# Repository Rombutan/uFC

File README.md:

# uFC

A baby flight controller main board optimized for small unpowered creations, powered by the esp32 and mpu6050.
Will soon have a camera connector.

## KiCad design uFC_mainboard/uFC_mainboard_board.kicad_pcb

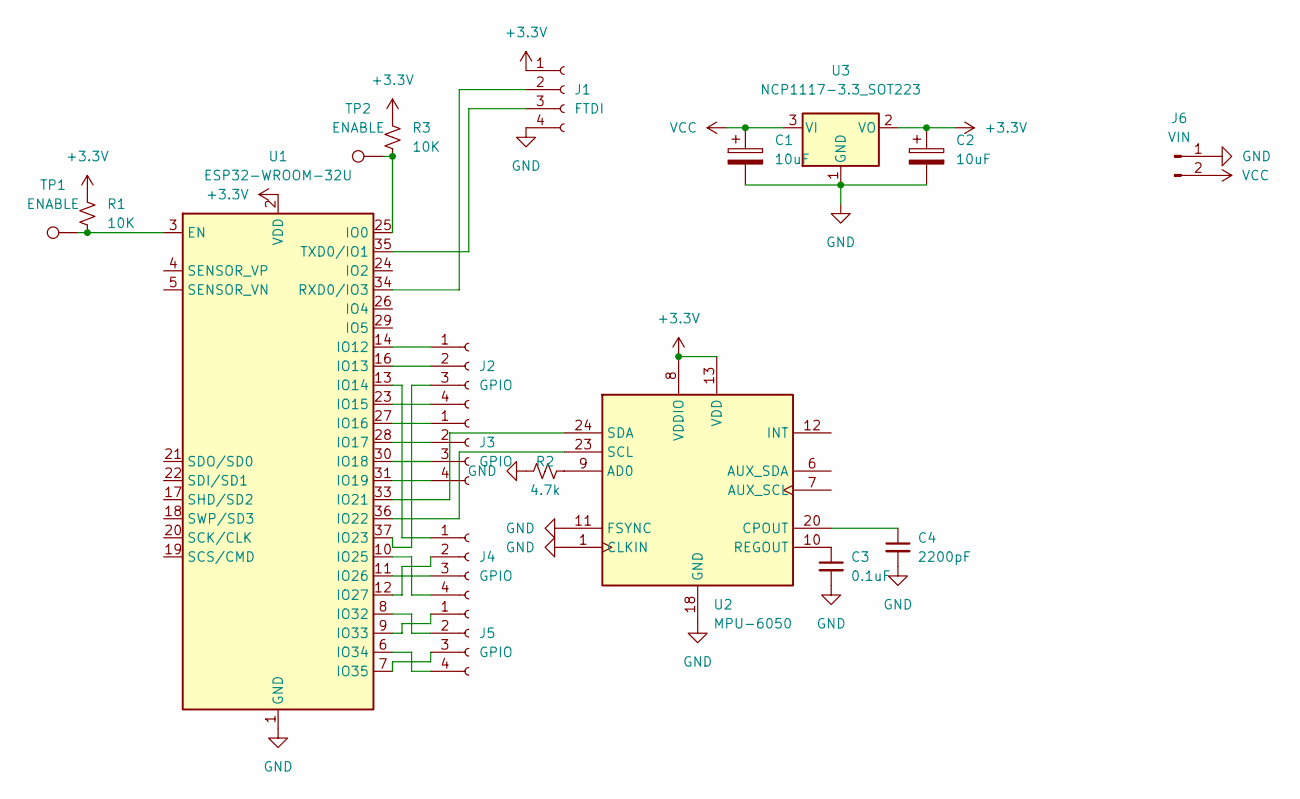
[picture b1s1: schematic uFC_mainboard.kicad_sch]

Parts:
C1, C2: 10uF; CP_Elec_4x5.3
C3: 0.1uF; C_0402_1005Metric
C4: 2200pF; C_0402_1005Metric
J1: FTDI; PinHeader_1x04_P2.54mm_Vertical
J2, J3, J4, J5: GPIO; PinHeader_1x04_P2.54mm_Vertical
J6: VIN; PinHeader_1x02_P2.54mm_Vertical
R1, R3: 10K; R_0402_1005Metric
R2: 4.7k; R_0402_1005Metric
TP1, TP2: ENABLE; PinHeader_1x01_P2.54mm_Vertical
U1: ESP32-WROOM-32U
U2: MPU-6050; InvenSense_QFN-24_4x4mm_P0.5mm
U3: NCP1117-3.3_SOT223; SOT-223-3_TabPin2

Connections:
+3V3: C2.1, J1.1, R1.1, R3.1, U1.2 (VDD), U2.8 (VDDIO), U2.13 (VDD), U3.2 (VO)
GND: C1.2, C2.2, C3.2, C4.2, J1.4, J6.1, R2.1, U1.1 (GND), U1.15 (GND), U1.38 (GND), U1.39 (GND), U2.1 (CLKIN), U2.11 (FSYNC), U2.18 (GND), U3.1 (GND)
unnamed: J1.2, U1.34 (RXD0/IO3)
unnamed: J1.3, U1.35 (TXD0/IO1)
unnamed: J2.1, U1.14 (IO12)
unnamed: J2.2, U1.16 (IO13)
unnamed: J2.4, U1.23 (IO15)
unnamed: J3.1, U1.27 (IO16)
unnamed: J3.2, U1.28 (IO17)
unnamed: J3.3, U1.30 (IO18)
unnamed: J3.4, U1.31 (IO19)
unnamed: R1.2, TP1.1, U1.3 (EN)
unnamed: R2.2, U2.9 (AD0)
unnamed: J5.4, U1.6 (IO34)
unnamed: J5.3, U1.7 (IO35)
unnamed: J5.2, U1.8 (IO32)
unnamed: J5.1, U1.9 (IO33)
unnamed: J4.4, U1.10 (IO25)
unnamed: J4.3, U1.11 (IO26)
unnamed: J4.2, U1.12 (IO27)
unnamed: J4.1, U1.13 (IO14)
unnamed: R3.2, TP2.1, U1.25 (IO0)
unnamed: U1.33 (IO21), U2.24 (SDA)
unnamed: U1.36 (IO22), U2.23 (SCL)
unnamed: J2.3, U1.37 (IO23)
unnamed: C3.1, U2.10 (REGOUT)
unnamed: C4.1, U2.20 (CPOUT)
VCC: C1.1, J6.2, U3.3 (VI)

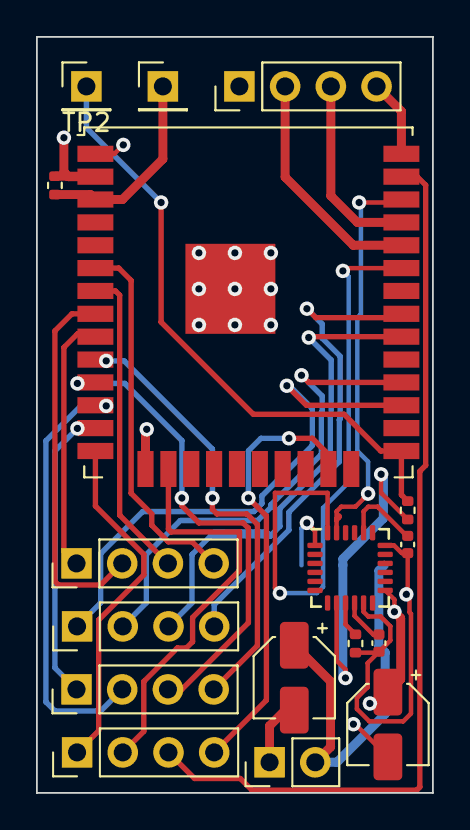
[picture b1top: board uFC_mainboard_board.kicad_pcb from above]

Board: 4 copper layers, 22.0 x 42.0 mm, 18 parts (1 on the bottom side), 28 nets.

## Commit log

2021-11-23 Update README.md
    comera != camera
2021-11-23 add license
